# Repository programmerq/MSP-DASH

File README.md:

# MSP-DASH

A digital gauge cluster for a turbocharged 2002 Mazda Miata (NB2) running rusEFI. Three round AMOLED screens show
gauges; one ESP32 "hub" reads the car (CAN bus and its own sensors) and sends everything to them over ESP-NOW.
A small OLED on the hub shows warning lamps and quick pages.

Power in the car (fuse, diode, TVS, buck options): docs/POWER.md.

The stock tach and speedo: `aircore/` (ESP32 DevKitC + two DRV8833 at 5 V, aircore build 8; set up on the hub's Stock gauges page). Pinout and calibration: aircore/README.md.

Current builds: **screens 245**, **hub 69**.

## Hardware

| Board | Role | Address |
|---|---|---|
| ESP32 DevKitC (Freenove terminal board) | **Hub**: CAN, sensors, buttons, brightness, OLED, GPS, accelerometer, 433 MHz | 192.168.55.204 |
| Waveshare ESP32-S3-Touch-AMOLED-1.43 (466x466) | **Left** screen | 192.168.55.201 |
| same | **Center** screen (also logs to its SD card) | 192.168.55.202 |
| same | **Right** screen | 192.168.55.203 |

Hub peripherals: SN65HVD230 CAN transceiver, MAX6675 (EGT), DHT22 (cabin temp/humidity), fuel level sender, GT-U7 GPS,
CC1101 433 MHz receiver (TPMS, in progress), 0.96" SSD1306 OLED, MPU6050 accelerometer, optional MCP23017 input
expanders, optional ADS1115 analog expanders, two page buttons, dash dimmer and lights-on inputs. Every GPIO with its terminal:
[docs/HUB_PINS.md](docs/HUB_PINS.md) (kept in step with `esp32-input/hub_pins.h` by a test).

## What it does

**Screens** (`esp32s3-amoled-bsp-base/`, LVGL 8 on Waveshare's BSP)
- Up to 8 named pages, each a 1-cell, 2-up, 3-up or 2x2 layout of needle, number, half-moon or trend-graph gauges, or
  a page of indicator lamps.
- Per gauge: signal, range, ticks, warning (flash or full-screen alert), peak hold, caption and value placement by
  coordinates, needle thickness and glow, 79 car icons (Material Design Icons) beside or instead of the caption.
- 10 contrast-checked colour schemes, switchable live from a button.
- Web editor with a live screen preview of each cell (caption, icon, sample value, colours), web dashboard,
  OTA updates.
- SD logging on the center screen: start conditions (key on, RPM, speed, any sensor), log files named by the GPS
  date and time, a time column, button log markers.
- Clock gauge from the GPS time (12/24 hour).

**Hub** (`esp32-input/`)
- rusEFI over CAN (DBC-matched), ECU detection, 16 configurable custom CAN sensors (`/custom`).
- Own sensors: EGT, cabin temp/humidity, fuel level, GPS speed/time, accelerometer (lateral, accel/brake and vertical
  G, yaw rate), lamp inputs.
- Brightness from the car's lights and dimmer (or a knob), with day/night levels.
- Inputs and pins page: every GPIO and expander pin with what uses it; move any function to another GPIO; up to 16 inputs on free pins as buttons (active LOW or HIGH, press and hold actions), switches or analog sensors (pressure, voltage, temperature presets, or custom) feeding custom sensor slots; up to 16 outputs (relays, LEDs) switched by a signal, an input or a button.
- Two buttons, configurable on `/buttons`: press or hold 1/2/3/5/10 s, left/right/both. Actions: next/previous page,
  choose screen, go to page, dim/brighten, colour scheme, race mode, clear warning, log marker, show IPs, OLED next page.
- OLED warning panel (`/oled`): 8 lamps with icons, WARNING and DANGER levels, signal or wire-input triggers, plus
  pages (big number, values, G-meter, clock); a lit lamp takes the screen over.
- Bench simulator (`/simulator`) that drives every screen without the car.
- One web app at the hub's address, with a side menu: Dashboard (status tiles, warning panel, key readings), Setup (brightness, clock, accelerometer, I2C devices), Screens (each screen's own pages, picked Left / Center / Right), OLED, Live and custom sensors, Buttons, Logging, Firmware, Simulator, Raw CAN, 433 MHz.

## Getting started

New PC setup (arduino-cli, ESP32 core 3.3.11, libraries, `lv_conf.h`): [PREREQUISITES.md](PREREQUISITES.md).
Copy `esp32-input/wifi_config.h.example` to `wifi_config.h` (and the same for the screens) with your WiFi details.

### Flashing (PowerShell)

Hub (it builds with a few shared headers from the screen folder, copied in first):

```powershell
cls
cd C:\Users\alejo\OneDrive\GIT\MSP-DASH
git pull origin main
copy C:\Users\alejo\OneDrive\GIT\MSP-DASH\esp32s3-amoled-bsp-base\can_parsing.h,C:\Users\alejo\OneDrive\GIT\MSP-DASH\esp32s3-amoled-bsp-base\can_flags.h,C:\Users\alejo\OneDrive\GIT\MSP-DASH\esp32s3-amoled-bsp-base\gauge_config.h,C:\Users\alejo\OneDrive\GIT\MSP-DASH\esp32s3-amoled-bsp-base\link_packets.h,C:\Users\alejo\OneDrive\GIT\MSP-DASH\esp32s3-amoled-bsp-base\simulator.h,C:\Users\alejo\OneDrive\GIT\MSP-DASH\esp32s3-amoled-bsp-base\simulator.cpp,C:\Users\alejo\OneDrive\GIT\MSP-DASH\esp32s3-amoled-bsp-base\custom_slots.h,C:\Users\alejo\OneDrive\GIT\MSP-DASH\esp32s3-amoled-bsp-base\color_presets.h,C:\Users\alejo\OneDrive\GIT\MSP-DASH\esp32s3-amoled-bsp-base\button_actions.h,C:\Users\alejo\OneDrive\GIT\MSP-DASH\esp32s3-amoled-bsp-base\gps_time.h C:\Users\alejo\OneDrive\GIT\MSP-DASH\esp32-input\
arduino-cli compile --clean --fqbn esp32:esp32:esp32:FlashFreq=40,FlashMode=dio,PartitionScheme=min_spiffs --build-path C:\esp32build-input C:\Users\alejo\OneDrive\GIT\MSP-DASH\esp32-input
curl.exe -s -H "Expect:" -w " HTTP %{http_code}" -F "firmware=@C:\esp32build-input\esp32-input.ino.bin" http://192.168.55.204/update
```

Screens (all three):

```powershell
cls
cd C:\Users\alejo\OneDrive\GIT\MSP-DASH
arduino-cli compile --clean --fqbn esp32:esp32:esp32s3:PSRAM=opi,FlashSize=16M,CDCOnBoot=cdc,PartitionScheme=app3M_fat9M_16MB --build-path C:\esp32build C:\Users\alejo\OneDrive\GIT\MSP-DASH\esp32s3-amoled-bsp-base
foreach ($ip in "192.168.55.201","192.168.55.202","192.168.55.203") { $r = curl.exe -s -H "Expect:" -w " HTTP %{http_code}" -F "firmware=@C:\esp32build\esp32s3-amoled-bsp-base.ino.bin" http://$ip/update; Write-Host "$ip -> $r" }
```

Or build with the commands above and upload from the hub's Firmware page: the hub, and all screens from one file.
If a board stops answering over WiFi, flash it over USB with `arduino-cli upload -p COMx --fqbn <same fqbn> --input-dir <build path> <sketch folder>`.

## Tests

Host tests run on a PC, no boards needed: [tests/host/README.md](tests/host/README.md). They cover the gauge config,
logging, simulator, button logic, GPS time, OLED panel and pages, accelerometer math, the CAN decoder, every web page's
script (in Node), a compile check of the whole hub sketch (`hub_typecheck.sh`) and of the screen sources
(`typecheck.sh`).

## Repository

| Path | What |
|---|---|
| `esp32s3-amoled-bsp-base/` | Screen firmware, plus the headers shared with the hub |
| `esp32-input/` | Hub firmware |
| `tests/host/` | Host tests and stubs |
| `tools/icons/` | Icon pipeline: Material Design Icons to LVGL fonts and 1-bit OLED bitmaps, previews |
| `tools/gen_fonts.sh` | Number fonts |
| `docs/` | Design notes, see below |

## Docs

| File | About |
|---|---|
| [CODE_GUIDE.md](docs/CODE_GUIDE.md) | How the code is organised, file by file |
| [HUB_PINS.md](docs/HUB_PINS.md) | Hub wiring, every GPIO with its terminal |
| [CAN-map.md](docs/CAN-map.md), [rusefi.dbc](docs/rusefi.dbc) | rusEFI CAN frames and decoding |
| [RUSEFI_LUA.md](docs/RUSEFI_LUA.md) | Lua script for EGT to rusEFI |
| [HUB_SPEED_SENSORS.md](docs/HUB_SPEED_SENSORS.md) | Hall speed sensor and GPS |
| [CONFIGURABLE_SENSORS.md](docs/CONFIGURABLE_SENSORS.md) | Custom CAN sensor slots |
| [HUB_433MHZ.md](docs/HUB_433MHZ.md) | CC1101 receiver and the TPMS decode work |
| [TODO.md](docs/TODO.md) | Tasks to be done, and the voltage divider values for 3.3 V inputs |
| [TIMELINE.md](docs/TIMELINE.md) | Build-by-build history |
| [esp32s3-amoled-board.md](docs/esp32s3-amoled-board.md) | Screen bring-up history and hardware findings |

## Status and next steps

Working on the bench: screens, hub, CAN from rusEFI, brightness, buttons, simulator, logging, OLED panel and pages, GPS,
accelerometer, the web app. Everything still open is in [docs/TODO.md](docs/TODO.md).

The old WROOM + Nextion firmware was removed in build 149 and early bring-up sketches in build 114; both are in git history.

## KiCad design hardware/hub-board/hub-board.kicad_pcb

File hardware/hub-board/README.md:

# Hub carrier board, rev A

The hub's ESP32 DevKitC plugs into two 19-pin sockets; every module plugs into a socket; the car's wiring goes to
5.08 mm screw terminals. 120 x 95 mm, 2 layers, through-hole only (hand soldering). Pins are the defaults in
docs/HUB_PINS.md; the board replaces the Freenove terminal board.

**Status: designed and routed, not built.** Design rules pass with no unconnected pads (drc.rpt). What is left in the
report is cosmetic (silkscreen text overlapping, footprint library links that resolve on a PC with KiCad's standard
libraries).

Files: `hub-board.kicad_pro` (open this in KiCad 7 or 8: it brings the schematic and the board), `hub-board.kicad_sch`,
`hub-board.kicad_pcb`, `hub-board-gerbers.zip` (upload to JLCPCB: 2 layers, 1.6 mm, 1 oz, any colour), `gerbers/`.

The schematic and the board are linked part by part, so a change in the schematic goes to the board with Tools >
Update PCB from Schematic. To use a different plug: change that connector's Footprint field in the schematic (for
example a JST-XH or Molex Micro-Fit footprint with the same number of pins), update the PCB, move the new part into
place and re-route its tracks. Parts are boxes with every pin named; pins with the same label are connected.

## Check before ordering

1. **DevKitC row spacing:** the board uses 25.4 mm between the two 19-pin rows. Measure yours.
2. **Module pin order** (each socket's pin 1 has the square pad). Clones differ: check yours against these.

| Socket | Module | Pins from pin 1 |
|---|---|---|
| J6 (2x4) | CC1101 | 1 GND, 2 VCC, 3 GDO0, 4 CSN, 5 SCK, 6 MOSI, 7 MISO, 8 GDO2 |
| J7 + J8 | SN65HVD230 | 3V3, GND, CTX, CRX + CANH, CANL |
| J9 | MAX6675 | GND, VCC, SCK, CS, SO |
| J10 | SSD1306 OLED | GND, VCC, SCL, SDA |
| J11 | MPU6050 GY-521 | VCC, GND, SCL, SDA, XDA, XCL, AD0, INT |
| J12 | ADS1115 | VDD, GND, SCL, SDA, ADDR, ALRT, A0, A1, A2, A3 |
| J13, J14 | I2C (MCP23017, spare) | 3V3, GND, SCL, SDA |
| J15 | GPS (NEO-6M) | VCC (5 V), RX, TX, GND |
| J16 | DHT22 | +, DATA, - |
| J4 | Buck module (wired) | IN+, IN-, OUT+, OUT- |
| J17 | Spare GPIO | IO0, IO2, IO12, GND |

3. **Fuel sender:** J22 goes through 1k with a 3.3 V clamp. R15 (pull-up to 3.3 V) is not fitted; fit it only if your
   sender wiring needs one.
4. **CAN termination:** most SN65HVD230 boards have 120 ohm already. JP1 adds R1 (120 ohm): fit the jumper only if the
   bus needs it.

## Parts (besides the modules)

| Ref | Part |
|---|---|
| F1 | Bourns MF-RG300 PTC fuse |
| D1 | 1N5822 (reverse polarity) |
| D2 | P6KE18A TVS |
| D3 | 1N5819 (5 V to the DevKitC, so USB and the car supply cannot feed each other) |
| C1 | 470 uF 35 V radial, 8 mm |
| C2 | 100 uF 10 V radial, 6.3 mm |
| R10, R12 | 47k; R11, R13 | 10k (lights and dimmer dividers) |
| R14 | 1k; R15 | pull-up, not fitted |
| D10-D12 | BZX79-C3V3 zener |
| C10-C12 | 100 nF disc |
| R1 | 120 ohm; JP1 | 2-pin header + jumper |
| J1, J2 | 1x19 female header 2.54 mm |
| J3, J5, J20-J25 | Phoenix MKDS 1,5 5.08 mm terminals (2, 3, 5 way) |
| Sockets | female headers 2.54 mm: 2x4, 1x2, 1x3, 1x4, 1x5, 1x8, 1x10 |
| H1-H4 | M3 mounting holes |

Traces are 0.5 mm (power included: the hub, screens and gauge board together draw well under 2 A); ground is poured on
both sides. The area under the ESP32's antenna (left end) has no copper.

## Regenerating

`tools/gen_hub_board.py` holds the parts list, placement and nets. With KiCad 7's Python:

```
python3 tools/gen_hub_board.py place                     # board with parts, and hub-board.dsn for the router
java -jar freerouting-2.0.1.jar --gui.enabled=false -de hub-board.dsn -do run.ses -mp 25 -mt 1
python3 tools/gen_hub_board.py finish hardware/hub-board/run.ses   # routes in, ground pours, DRC
```

Freerouting 2.0.1 single-threaded (`-mt 1`): multi-threaded and 2.1.0 runs left connections out of the .ses. If DRC
still lists unconnected pads, export a DSN from that board and route it once more (the second pass keeps the first
pass's tracks and adds the rest); that is how this board's `hub-board.ses` was made.

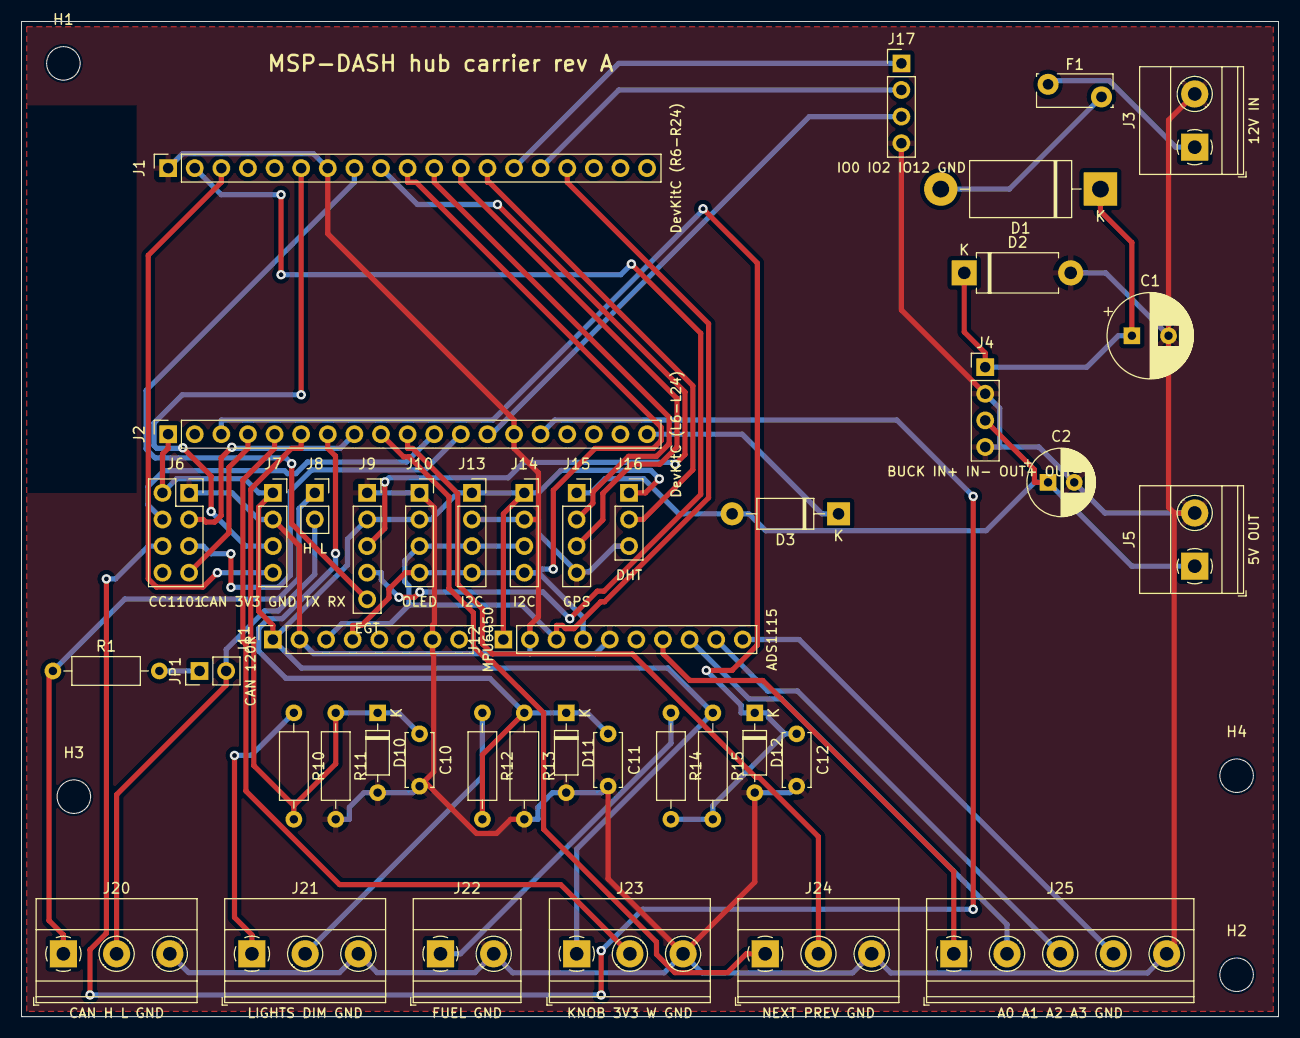
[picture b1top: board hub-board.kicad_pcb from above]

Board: 2 copper layers, 120.0 x 95.0 mm, 47 parts (0 on the bottom side), 41 nets.

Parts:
C1: 470uF 35V; CP_Radial_D8.0mm_P3.50mm
C2: 100uF 10V; CP_Radial_D6.3mm_P2.50mm
C10, C11, C12: 100nF; C_Disc_D5.0mm_W2.5mm_P5.00mm
D1: 1N5822; D_DO-201AD_P15.24mm_Horizontal
D2: P6KE18A TVS; D_DO-15_P10.16mm_Horizontal
D3: 1N5819; D_DO-41_SOD81_P10.16mm_Horizontal
D10, D11, D12: BZX79-C3V3; D_DO-35_SOD27_P7.62mm_Horizontal
F1: MF-RG300 PTC; Fuse_Bourns_MF-RG300
H1, H2, H3, H4: M3; MountingHole_3.2mm_M3
J1: DevKitC (R6-R24); PinSocket_1x19_P2.54mm_Vertical
J2: DevKitC (L6-L24); PinSocket_1x19_P2.54mm_Vertical
J3: 12V IN; TerminalBlock_Phoenix_MKDS-1,5-2-5.08_1x02_P5.08mm_Horizont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
J4: BUCK IN+ IN- OUT+ OUT-; PinHeader_1x04_P2.54mm_Vertical
J5: 5V OUT; TerminalBlock_Phoenix_MKDS-1,5-2-5.08_1x02_P5.08mm_Horizont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
J6: CC1101; PinSocket_2x04_P2.54mm_Vertical
J7: CAN 3V3 GND TX RX; PinSocket_1x04_P2.54mm_Vertical
J8: H L; PinSocket_1x02_P2.54mm_Vertical
J9: EGT; PinSocket_1x05_P2.54mm_Vertical
J10: OLED; PinSocket_1x04_P2.54mm_Vertical
J11: MPU6050; PinSocket_1x08_P2.54mm_Vertical
J12: ADS1115; PinSocket_1x10_P2.54mm_Vertical
J13, J14: I2C; PinSocket_1x04_P2.54mm_Vertical
J15: GPS; PinSocket_1x04_P2.54mm_Vertical
J16: DHT; PinSocket_1x03_P2.54mm_Vertical
J17: IO0 IO2 IO12 GND; PinHeader_1x04_P2.54mm_Vertical
J20: CAN H L GND; TerminalBlock_Phoenix_MKDS-1,5-3-5.08_1x03_P5.08mm_Horizont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
J21: LIGHTS DIM GND; TerminalBlock_Phoenix_MKDS-1,5-3-5.08_1x03_P5.08mm_Horizont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
J22: FUEL GND; TerminalBlock_Phoenix_MKDS-1,5-2-5.08_1x02_P5.08mm_Horizont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
J23: KNOB 3V3 W GND; TerminalBlock_Phoenix_MKDS-1,5-3-5.08_1x03_P5.08mm_Horizont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
J24: NEXT PREV GND; TerminalBlock_Phoenix_MKDS-1,5-3-5.08_1x03_P5.08mm_Horizont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
J25: A0 A1 A2 A3 GND; TerminalBlock_Phoenix_MKDS-1,5-5-5.08_1x05_P5.08mm_Horizont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
JP1: CAN 120R; PinHeader_1x02_P2.54mm_Vertical
R1: 120R; R_Axial_DIN0207_L6.3mm_D2.5mm_P10.16mm_Horizontal
R10, R12: 47k; R_Axial_DIN0207_L6.3mm_D2.5mm_P10.16mm_Horizontal
R11, R13: 10k; R_Axial_DIN0207_L6.3mm_D2.5mm_P10.16mm_Horizontal
R14: 1k; R_Axial_DIN0207_L6.3mm_D2.5mm_P10.16mm_Horizontal
R15: DNP (pull-up); R_Axial_DIN0207_L6.3mm_D2.5mm_P10.16mm_Horizontal

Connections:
12V_F: D1.2, F1.2
12V_IN: F1.1, J3.1
+3V3: J2.1, J6.2, J7.1, J9.2, J10.2, J11.1, J12.1, J13.1, J14.1, J16.1, J23.1, R15.1
+5V: C2.1, D3.2, J4.3, J5.1, J15.1
+5V_ESP: D3.1, J2.19
+12V: C1.1, D1.1, D2.1, J4.1
ADS_A0: J12.7, J25.1
ADS_A1: J12.8, J25.2
ADS_A2: J12.9, J25.3
ADS_A3: J12.10, J25.4
BTN_NEXT: J2.9, J24.1
BTN_PREV: J2.10, J24.2
CANH: J8.1, J20.1, R1.1
CANL: J8.2, J20.2, JP1.2
CAN_RX: J1.3, J7.4
CAN_T: JP1.1, R1.2
CAN_TX: J1.6, J7.3
DHT_DATA: J1.13, J16.2
DIMMER: C11.1, D11.1, J2.7, R12.2, R13.1
DIMMER_12V: J21.2, R12.1
EGT_CS: J1.2, J9.4
EGT_SCK: J1.9, J9.3
EGT_SO: J1.8, J9.5
FUEL: C12.1, D12.1, J2.3, R14.2, R15.2
FUEL_IN: J22.1, R14.1
GND: C1.2, C2.2, C10.2, C11.2, C12.2, D2.2, D10.2, D11.2, D12.2, J1.1, J1.7, J2.14, J3.2, J4.2, J4.4, J5.2, J6.1, J7.2, J9.1, J10.1, J11.2, J11.7, J12.2, J12.5, J13.2, J14.2, J15.4, J16.3, J17.4, J20.3, J21.3, J22.2, J23.3, J24.3, J25.5, R11.2, R13.2
GPS_RXD: J1.11, J15.2
GPS_TXD: J1.12, J15.3
I2C_SCL: J1.16, J10.3, J11.3, J12.3, J13.3, J14.3
I2C_SDA: J1.10, J10.4, J11.4, J12.4, J13.4, J14.4
KNOB: J2.5, J23.2
LIGHTS: C10.1, D10.1, J2.6, R10.2, R11.1
LIGHTS_12V: J21.1, R10.1
RF_CSN: J2.11, J6.4
RF_GDO0: J2.8, J6.3
RF_MISO: J2.4, J6.7
RF_MOSI: J2.15, J6.6
RF_SCK: J2.12, J6.5
SPARE_IO0: J1.14, J17.1
SPARE_IO2: J1.15, J17.2
SPARE_IO12: J2.13, J17.3

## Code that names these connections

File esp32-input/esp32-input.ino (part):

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//
// Bench board: ESP32-D (classic ESP32, fqbn esp32:esp32:esp32:FlashFreq=40,FlashMode=dio: at the default 80 MHz this board
// boot-looped reading garbage from flash). Later: the S2 Mini (change the pins below).
// Car inputs (see the web page at this board's IP for settings): lights-on wire -> 47k -> GPIO 35, and 10k from GPIO 35 to GND;
//   dimmer wire the same into GPIO 32 (add 10 uF from GPIO 32 to GND if the dimmer is PWM).
// Wiring: buttons to GND on any free pin (internal pull-ups), or several on one analog pin through resistors (Buttons page),
//         10k knob: outer legs to 3.3 V and GND, middle leg to POT_PIN (ADC1 only: ADC2 doesn't work with the radio on).
// Copy wifi_config.h.example to wifi_config.h and fill in the network, the same one the screens use.

#include "hub_pins.h"         // every GPIO the hub uses: roles, defaults, what each GPIO can do (docs/HUB_PINS.md)
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// Where each signal last came from, for the /sensors page: a CAN ID, or one of the hub's own sensors.
#define SRC_HUB_EGT  0xFFFF0001u   // MAX6675
#define SRC_HUB_DHT  0xFFFF0002u   // DHT22
#define SRC_HUB_FUEL 0xFFFF0003u   // fuel pot / sender
#define SRC_HUB_SIM  0xFFFF0004u   // the bench simulator
#define SRC_HUB_GPS  0xFFFF0006u   // GPS
#define SRC_HUB_IMU  0xFFFF0007u   // MPU6050 accelerometer
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  return v;
}
static void egtTask(void *) {
  pinMode(EGT_CS, OUTPUT); digitalWrite(EGT_CS, HIGH);
  pinMode(EGT_SCK, OUTPUT); digitalWrite(EGT_SCK, LOW);
  pinMode(EGT_SO, INPUT);
  vTaskDelay(pdMS_TO_TICKS(500));                   // first conversion after power-up
  for (;;) {
    uint16_t raw = max6675Read();
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  }
}

// ---- Fuel level: pot (mock sender) on GPIO36, 0-3.3 V = 0-100 %, smoothed, read every 100 ms ----
static volatile float s_fuelPct = 0;   // the pot's own reading, shown on the home page even while the simulator runs
static void fuelTask(void *) {
  float avg = adcRaw(FUEL_PIN);
  for (;;) {
    avg += (adcRaw(FUEL_PIN) - avg) * 0.1f;      // slow filter: fuel sloshes, the gauge should not
    s_fuelPct = avg * 100.0f / 4095.0f;
    if (simOwns()) { vTaskDelay(pdMS_TO_TICKS(100)); continue; }
    g_fuel_pct = avg * 100.0f / 4095.0f;
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static void readKnob() {
  int raw = adcRaw(POT_PIN);
  s_potAvg = s_potAvg < 0 ? raw : s_potAvg * 0.85f + raw * 0.15f;
  s_lightsV = s_lightsV * 0.8f + carVolts(LIGHTS_PIN) * 0.2f;
  s_dimV = s_dimV * 0.8f + carVolts(DIMMER_PIN) * 0.2f;
  int pct = finalPct();
  if (s_briPct < 0 || abs(pct - s_briPct) >= 2 || millis() - s_lastBriMs > 2000) {
    s_briPct = pct; s_lastBriMs = millis();
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  imuLoad();     // accelerometer mounting and zero
  pagesLoad();   // OLED pages
  // CAN: the hub is now the only CAN reader; the screens are all remotes
  twai_general_config_t g = TWAI_GENERAL_CONFIG_DEFAULT(CAN_TX_PIN, CAN_RX_PIN, TWAI_MODE_NORMAL);
  g.rx_queue_len = 64;
  twai_timing_config_t t = TWAI_TIMING_CONFIG_500KBITS();
  twai_filter_config_t f = TWAI_FILTER_CONFIG_ACCEPT_ALL();
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  else { can_start_task(); Serial.println("CAN running on GPIO 21 (TX) / 22 (RX)"); }
  xTaskCreatePinnedToCore(egtTask, "egt", 3072, NULL, 2, NULL, 1);
  xTaskCreatePinnedToCore(dhtTask, "dht", 3072, NULL, 2, NULL, 1);
  xTaskCreatePinnedToCore(fuelTask, "fuel", 2048, NULL, 1, NULL, 1);
  xTaskCreatePinnedToCore(gpsTask, "gps", 4096, NULL, 2, NULL, 1);
  xTaskCreatePinnedToCore(canTxTask, "can_tx", 3072, NULL, 2, NULL, 1);
  rfBegin();   // CC1101 on GPIO 13/14/27/33/39; carries on without it if not wired
  xTaskCreatePinnedToCore(oledTask, "oled", 4096, NULL, 1, NULL, 1);   // OLED panel; carries on without it if not wired
  xTaskCreatePinnedToCore(dataTask, "espnow_tx", 4096, NULL, 2, NULL, 0);
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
